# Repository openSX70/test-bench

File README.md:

# test-bench
universal SX70 PCB testes

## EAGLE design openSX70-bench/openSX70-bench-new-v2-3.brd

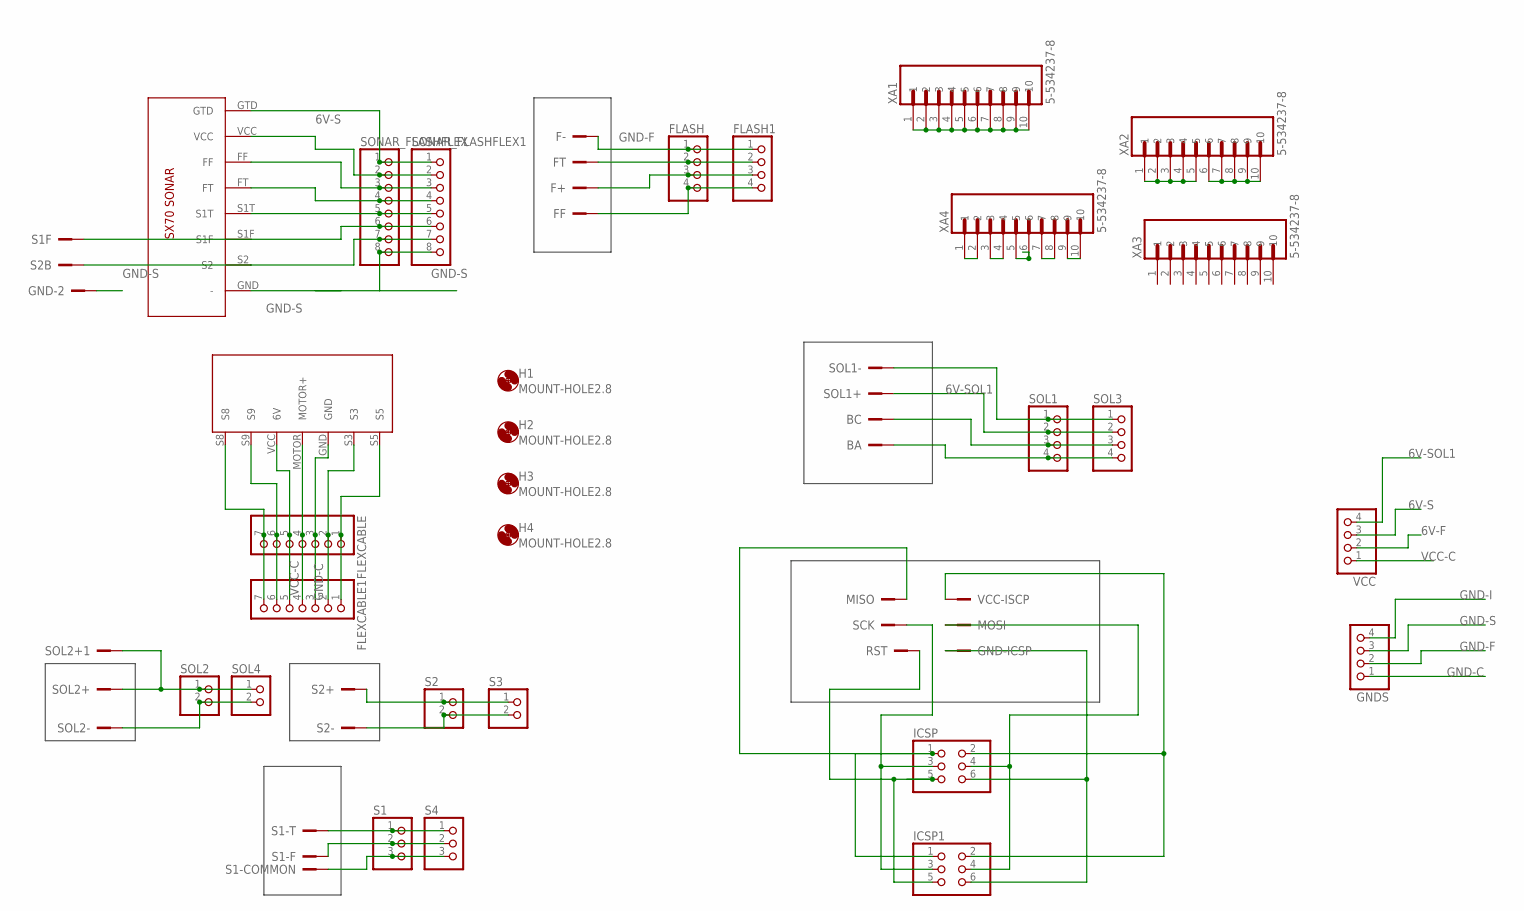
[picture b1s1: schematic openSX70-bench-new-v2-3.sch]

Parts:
BA: PINHEAD; 1X01
BC: PINHEAD; 1X01
F+: PINHEAD; 1X01
F-: PINHEAD; 1X01
FF: PINHEAD; 1X01
FLASH, FLASH1: PINHD-1X4; 1X04
FLEXCABLE, FLEXCABLE1: PINHD-1X7; 1X07
FT: PINHEAD; 1X01
GND-2: PINHEAD; 1X01
GND-ICSP: PINHEAD; 1X01
GNDS: PINHD-1X4; 1X04
H1, H2, H3, H4: MOUNT-HOLE2.8; 2,8
ICSP, ICSP1: PINHD-2X3; 2X03
MISO: PINHEAD; 1X01
MOSI: PINHEAD; 1X01
RST: PINHEAD; 1X01
S1, S4: PINHD-1X3; 1X03
S1-COMMON, S1-F, S1-T, S1F, S2+, S2-, S2B: PINHEAD; 1X01
S2, S3: PINHD-1X2; 1X02
SCK: PINHEAD; 1X01
SOL1, SOL3: PINHD-1X4; 1X04
SOL1+, SOL1-, SOL2+, SOL2+1, SOL2-: PINHEAD; 1X01
SOL2, SOL4: PINHD-1X2; 1X02
SONAR_FLASHFLEX, SONAR_FLASHFLEX1: PINHD-1X8; 1X08
U$1: SX70-7-PAD-HOLES-PROPER2
U$2: SX70-SONAR-FLASHFLEX-HOLES; SONAR-FLASHFLEX-HOLES
VCC: PINHD-1X4; 1X04
VCC-ISCP: PINHEAD; 1X01
XA1, XA2, XA3, XA4: 5-534237-8; TE_5-534237-8

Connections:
6V-F: F+.1, FLASH.3, FLASH1.3, VCC.2
6V-I: ICSP.2, ICSP1.2, VCC-ISCP.1
6V-S: SONAR_FLASHFLEX.2, SONAR_FLASHFLEX1.2, U$2.VCC, VCC.3
6V-SOL1: SOL1.2, SOL1+.1, SOL3.2, VCC.4
GND-C: FLEXCABLE.3, FLEXCABLE1.3, GNDS.1, U$1.GND
GND-F: F-.1, FLASH.1, FLASH1.1, GNDS.2
GND-I: GND-ICSP.1, GNDS.4, ICSP.6, ICSP1.6
GND-S: GND-2.1, GNDS.3, SONAR_FLASHFLEX.8, SONAR_FLASHFLEX1.8, U$2.GND (-)
unnamed: FLEXCABLE.7, FLEXCABLE1.7, U$1.S8
unnamed: FLEXCABLE.6, FLEXCABLE1.6, U$1.S9
unnamed: XA1.1, XA1.2, XA1.3, XA1.4, XA1.5, XA1.6, XA1.7, XA1.8, XA1.9, XA1.10
unnamed: FLEXCABLE.4, FLEXCABLE1.4, U$1.MOTOR (MOTOR+)
unnamed: XA4.1, XA4.2
unnamed: FLEXCABLE.2, FLEXCABLE1.2, U$1.S3
unnamed: FLEXCABLE.1, FLEXCABLE1.1, U$1.S5
unnamed: ICSP.1, ICSP1.1, MISO.1
unnamed: ICSP.3, ICSP1.3, SCK.1
unnamed: ICSP.5, ICSP1.5, RST.1
unnamed: XA4.3, XA4.4
unnamed: ICSP.4, ICSP1.4, MOSI.1
unnamed: S1F.1, SONAR_FLASHFLEX.6, SONAR_FLASHFLEX1.6, U$2.S1F
unnamed: SONAR_FLASHFLEX.5, SONAR_FLASHFLEX1.5, U$2.S1T
unnamed: SONAR_FLASHFLEX.1, SONAR_FLASHFLEX1.1, U$2.GTD
unnamed: SONAR_FLASHFLEX.3, SONAR_FLASHFLEX1.3, U$2.FF
unnamed: SONAR_FLASHFLEX.4, SONAR_FLASHFLEX1.4, U$2.FT
unnamed: XA4.5, XA4.6
unnamed: XA4.7, XA4.8
unnamed: S1.3, S1-COMMON.1, S4.3
unnamed: S1.2, S1-F.1, S4.2
unnamed: FLASH.2, FLASH1.2, FT.1
unnamed: S1.1, S1-T.1, S4.1
unnamed: FF.1, FLASH.4, FLASH1.4
unnamed: SOL1.1, SOL1-.1, SOL3.1
unnamed: XA4.9, XA4.10
unnamed: BC.1, SOL1.3, SOL3.3
unnamed: BA.1, SOL1.4, SOL3.4
unnamed: XA2.1, XA2.2, XA2.3, XA2.4, XA2.5
unnamed: XA2.6, XA2.7, XA2.8, XA2.9, XA2.10
unnamed: SOL2.1, SOL2+.1, SOL2+1.1, SOL4.1
unnamed: SOL2.2, SOL2-.1, SOL4.2
unnamed: S2.1, S2+.1, S3.1
unnamed: S2.2, S2-.1, S3.2
VCC-C: FLEXCABLE.5, FLEXCABLE1.5, U$1.VCC (6V), VCC.1

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
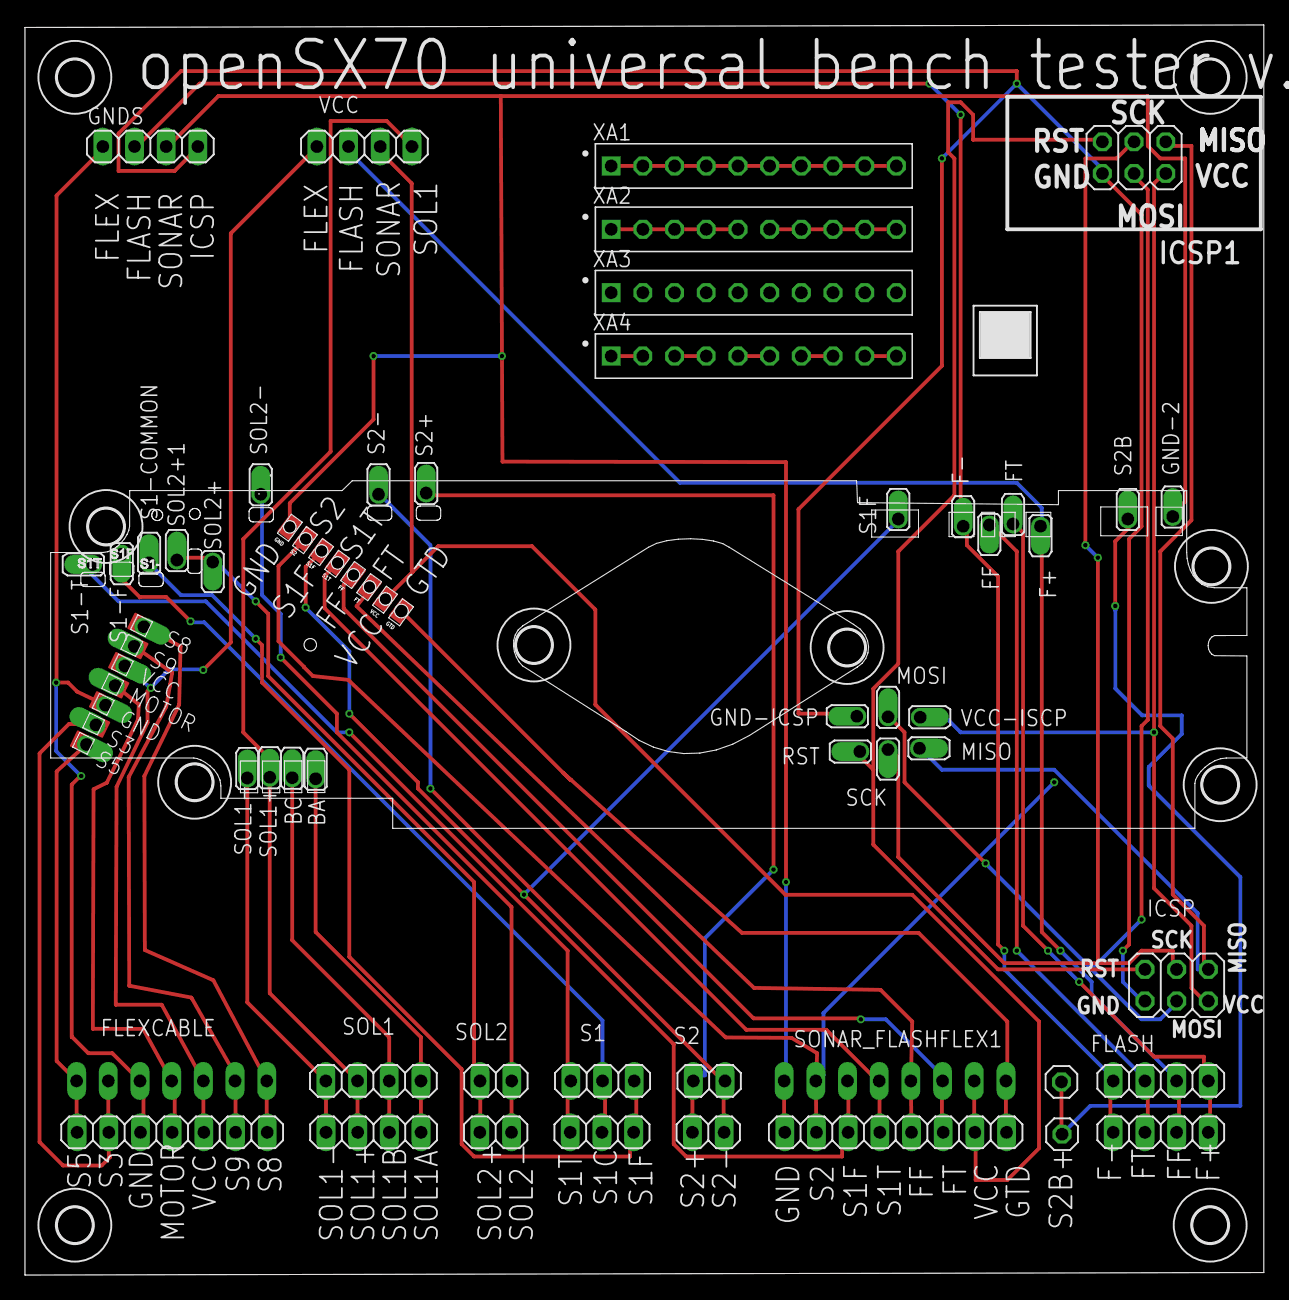
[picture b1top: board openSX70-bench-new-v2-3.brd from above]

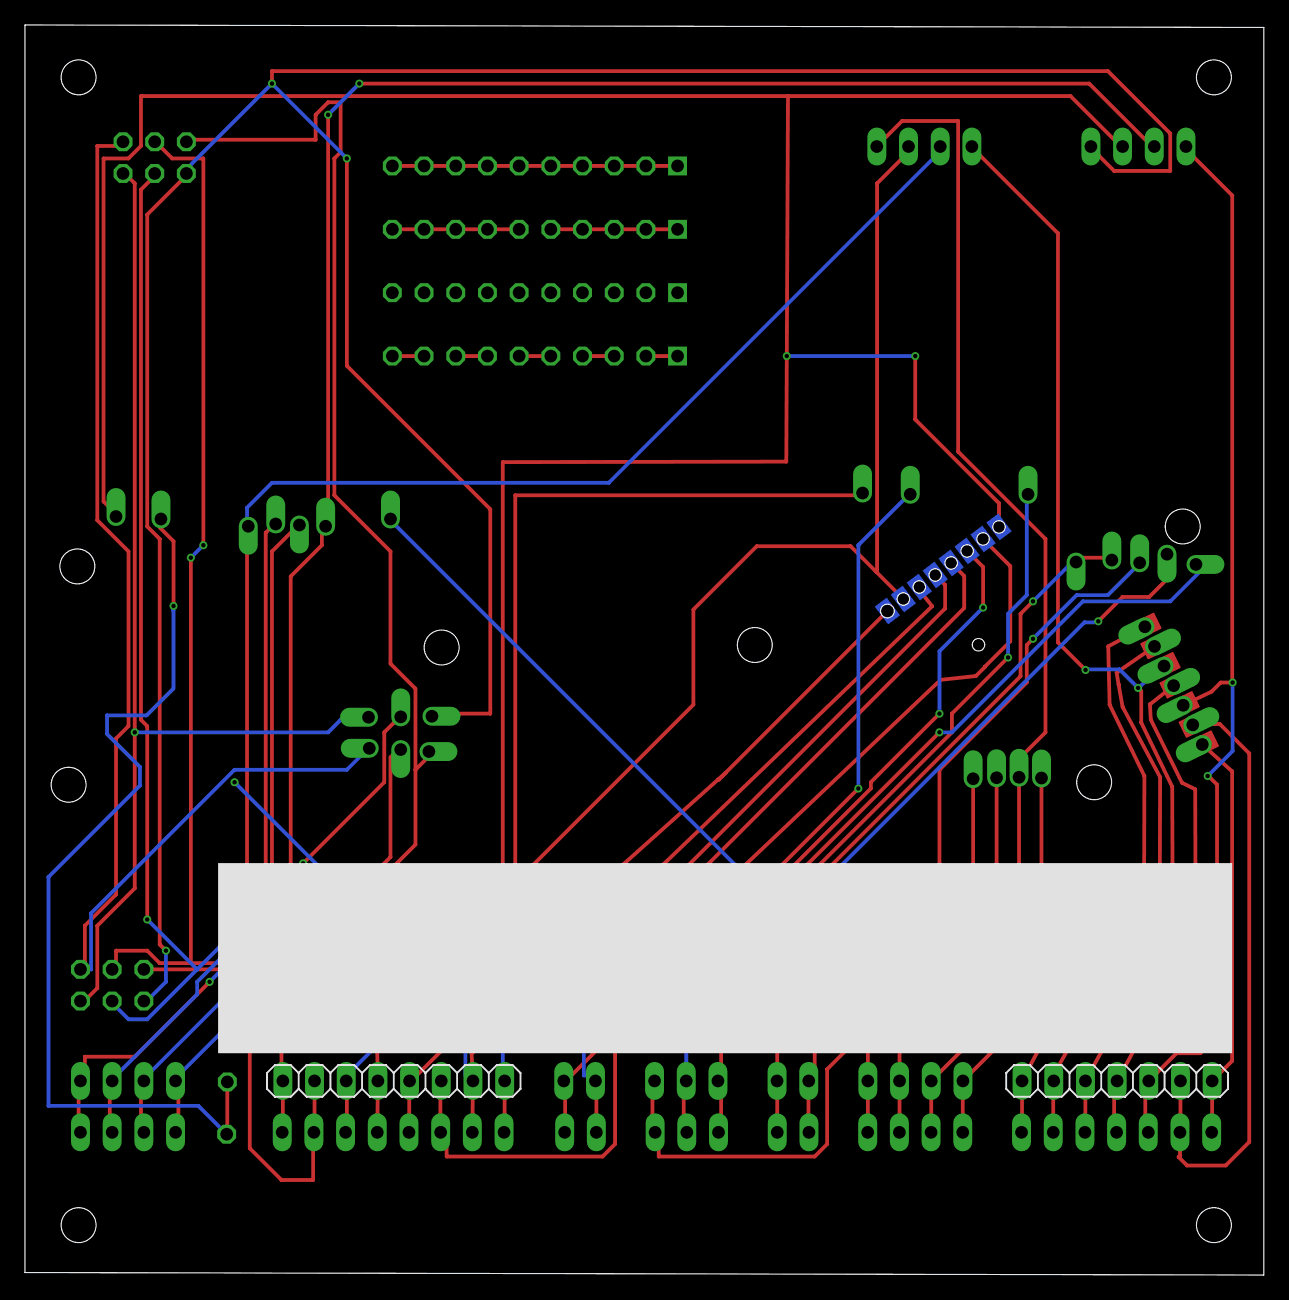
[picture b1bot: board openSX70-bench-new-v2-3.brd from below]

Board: 2 copper layers, 99.3 x 100.2 mm, 61 parts (2 on the bottom side), 45 nets.

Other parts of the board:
H5, H6, H7, H8, H9, H10: MOUNT-HOLE2.8; 2,8
JP1, JP2: 1X01

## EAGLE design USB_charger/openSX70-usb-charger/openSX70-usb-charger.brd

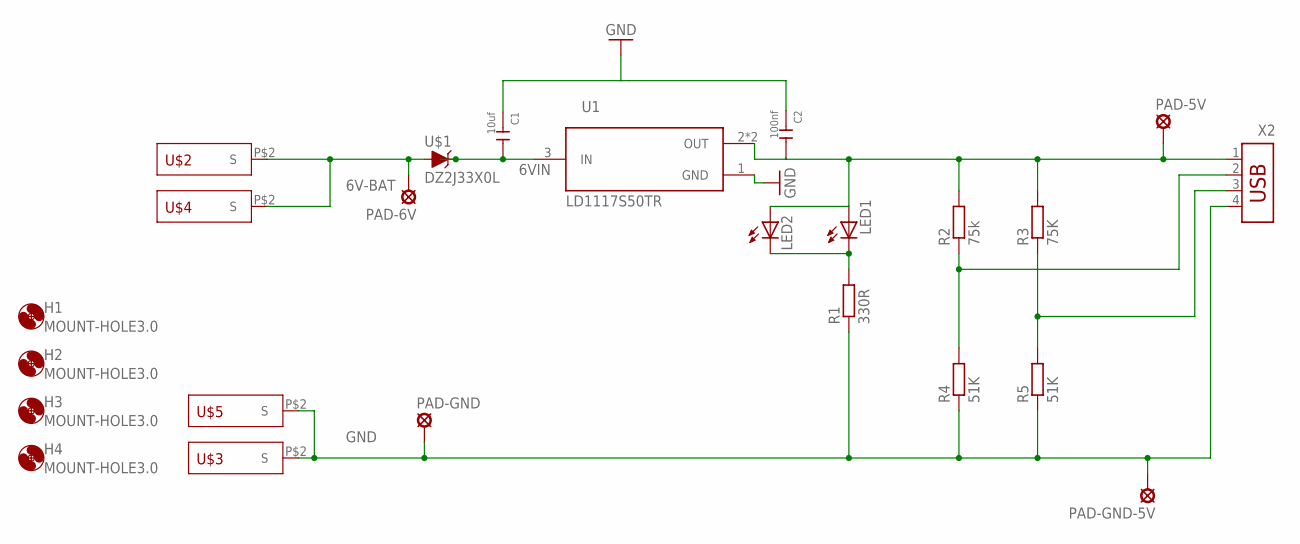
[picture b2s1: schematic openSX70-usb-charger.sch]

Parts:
C1: 10uf; C0603
C2: 100nf; C0603
H1, H2, H3, H4: MOUNT-HOLE3.0; 3,0
LED1: LED5MM
LED2: LEDCHIPLED_0805; CHIPLED_0805
PAD-5V, PAD-6V: LSP13
PAD-GND: LSP13
PAD-GND-5V: LSP13
R1: 330R; R0603
R2: 75k; R0603
R3: 75K; R0603
R4, R5: 51K; R0603
U1: LD1117S50TR; LD1117S50TR_SOT230P700X180-4N
U$1: DZ2J33X0L; SMINI2
U$2, U$3, U$4, U$5: BATTERY-PAD
X2: USB-787616; USB

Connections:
6V-BAT: PAD-6V.MP, U$1.P$2 (A), U$2.P$2, U$4.P$2
6VIN: C1.2, U1.3 (IN), U$1.P$1 (C)
GND: C1.1, C2.1, PAD-GND.MP, PAD-GND-5V.MP, R1.1, R4.1, R5.1, U1.1 (GND), U$3.P$2, U$5.P$2, X2.4
unnamed: LED1.K (C), LED2.C, R1.2
unnamed: C2.2, LED1.A, LED2.A, PAD-5V.MP, R2.2, R3.2, U1.2 (OUT), U1.4 (OUT), X2.1
unnamed: R2.1, R4.2, X2.2
unnamed: R3.1, R5.2, X2.3

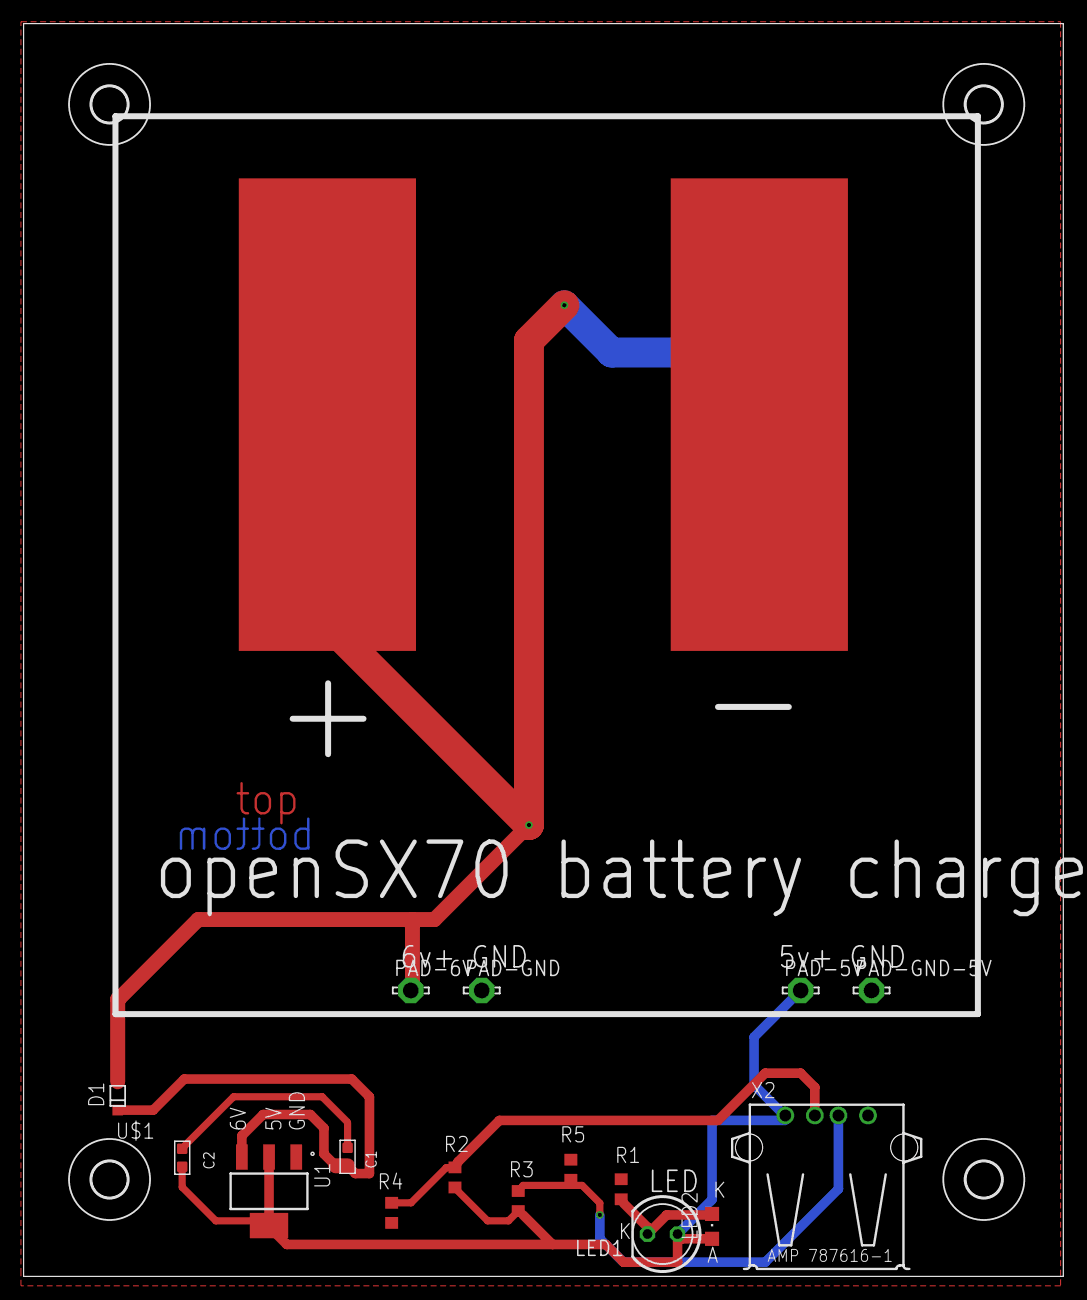
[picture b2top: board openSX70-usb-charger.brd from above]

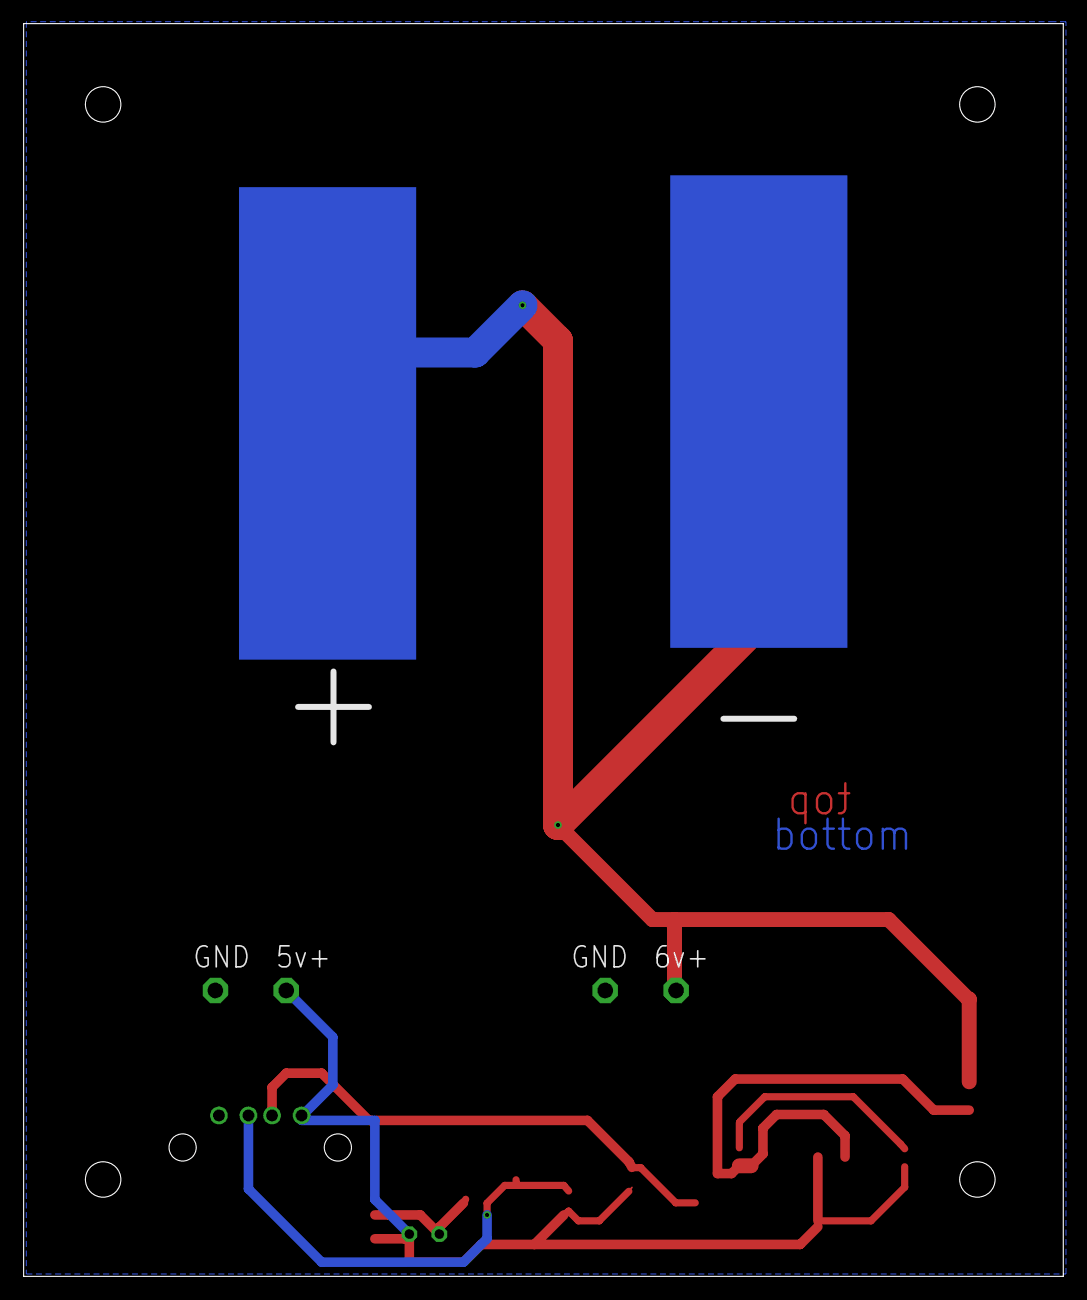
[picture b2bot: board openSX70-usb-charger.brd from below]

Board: 2 copper layers, 88.0 x 106.0 mm, 24 parts (2 on the bottom side), 7 nets.

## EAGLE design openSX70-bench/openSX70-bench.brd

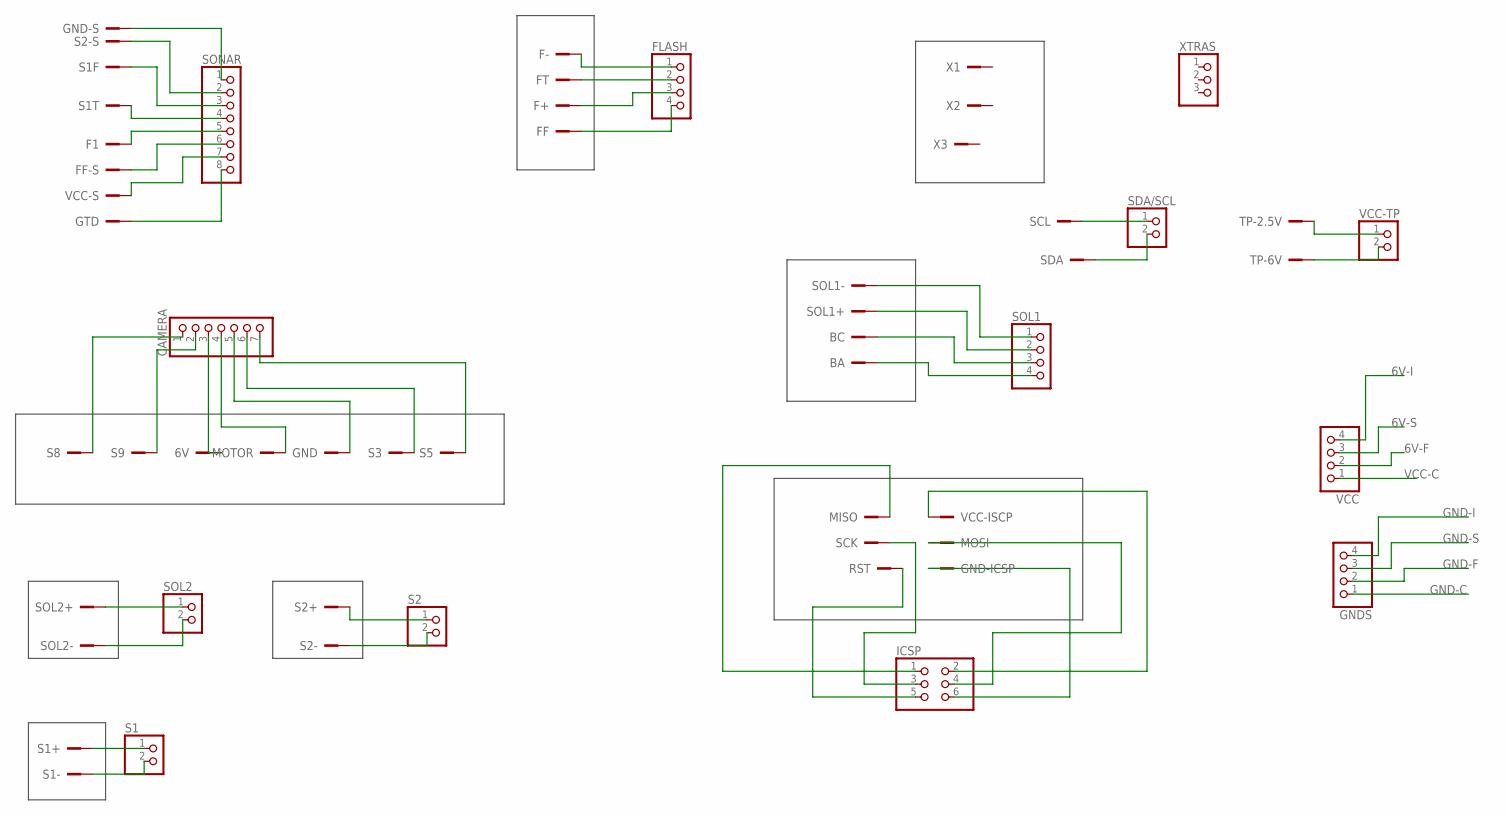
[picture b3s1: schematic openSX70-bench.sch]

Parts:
6V: PINHEAD; 1X01
BA: PINHEAD; 1X01
BC: PINHEAD; 1X01
CAMERA: PINHD-1X7; 1X07
F1: PINHEAD; 1X01
F+: PINHEAD; 1X01
F-: PINHEAD; 1X01
FF: PINHEAD; 1X01
FF-S: PINHEAD; 1X01
FLASH: PINHD-1X4; 1X04
FT: PINHEAD; 1X01
GND: PINHEAD; 1X01
GND-ICSP: PINHEAD; 1X01
GND-S: PINHEAD; 1X01
GNDS: PINHD-1X4; 1X04
GTD: PINHEAD; 1X01
ICSP: PINHD-2X3; 2X03
MISO: PINHEAD; 1X01
MOSI: PINHEAD; 1X01
MOTOR: PINHEAD; 1X01
RST: PINHEAD; 1X01
S1, S2: PINHD-1X2; 1X02
S1+, S1-, S1F, S1T, S2+, S2-, S2-S, S3, S5, S8, S9: PINHEAD; 1X01
SCK: PINHEAD; 1X01
SCL: PINHEAD; 1X01
SDA: PINHEAD; 1X01
SDA/SCL: PINHD-1X2; 1X02
SOL1: PINHD-1X4; 1X04
SOL1+, SOL1-, SOL2+, SOL2-: PINHEAD; 1X01
SOL2: PINHD-1X2; 1X02
SONAR: PINHD-1X8; 1X08
TP-2.5V, TP-6V: PINHEAD; 1X01
VCC: PINHD-1X4; 1X04
VCC-ISCP: PINHEAD; 1X01
VCC-S: PINHEAD; 1X01
VCC-TP: PINHD-1X2; 1X02
X1, X2, X3: PINHEAD; 1X01
XTRAS: PINHD-1X3; 1X03

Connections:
6V-F: F+.1, FLASH.3, VCC.2
6V-I: ICSP.2, VCC.4, VCC-ISCP.1
6V-S: SONAR.7, VCC.3, VCC-S.1
GND-C: CAMERA.5, GND.1, GNDS.1
GND-F: F-.1, FLASH.1, GNDS.2
GND-I: GND-ICSP.1, GNDS.4, ICSP.6
GND-S: GND-S.1, GNDS.3, SONAR.1
unnamed: CAMERA.1, S8.1
unnamed: CAMERA.2, S9.1
unnamed: CAMERA.4, MOTOR.1
unnamed: CAMERA.6, S3.1
unnamed: CAMERA.7, S5.1
unnamed: ICSP.1, MISO.1
unnamed: ICSP.3, SCK.1
unnamed: ICSP.5, RST.1
unnamed: ICSP.4, MOSI.1
unnamed: S2-S.1, SONAR.2
unnamed: S1F.1, SONAR.3
unnamed: S1T.1, SONAR.4
unnamed: F1.1, SONAR.5
unnamed: FF-S.1, SONAR.6
unnamed: GTD.1, SONAR.8
unnamed: FLASH.2, FT.1
unnamed: FF.1, FLASH.4
unnamed: SOL1.1, SOL1-.1
unnamed: SOL1.2, SOL1+.1
unnamed: BC.1, SOL1.3
unnamed: BA.1, SOL1.4
unnamed: SCL.1, SDA/SCL.1
unnamed: SDA.1, SDA/SCL.2
unnamed: TP-2.5V.1, VCC-TP.1
unnamed: TP-6V.1, VCC-TP.2
unnamed: SOL2.1, SOL2+.1
unnamed: SOL2.2, SOL2-.1
unnamed: S1.1, S1+.1
unnamed: S1.2, S1-.1
unnamed: S2.1, S2+.1
unnamed: S2.2, S2-.1
VCC-C: 6V.1, CAMERA.3, VCC.1

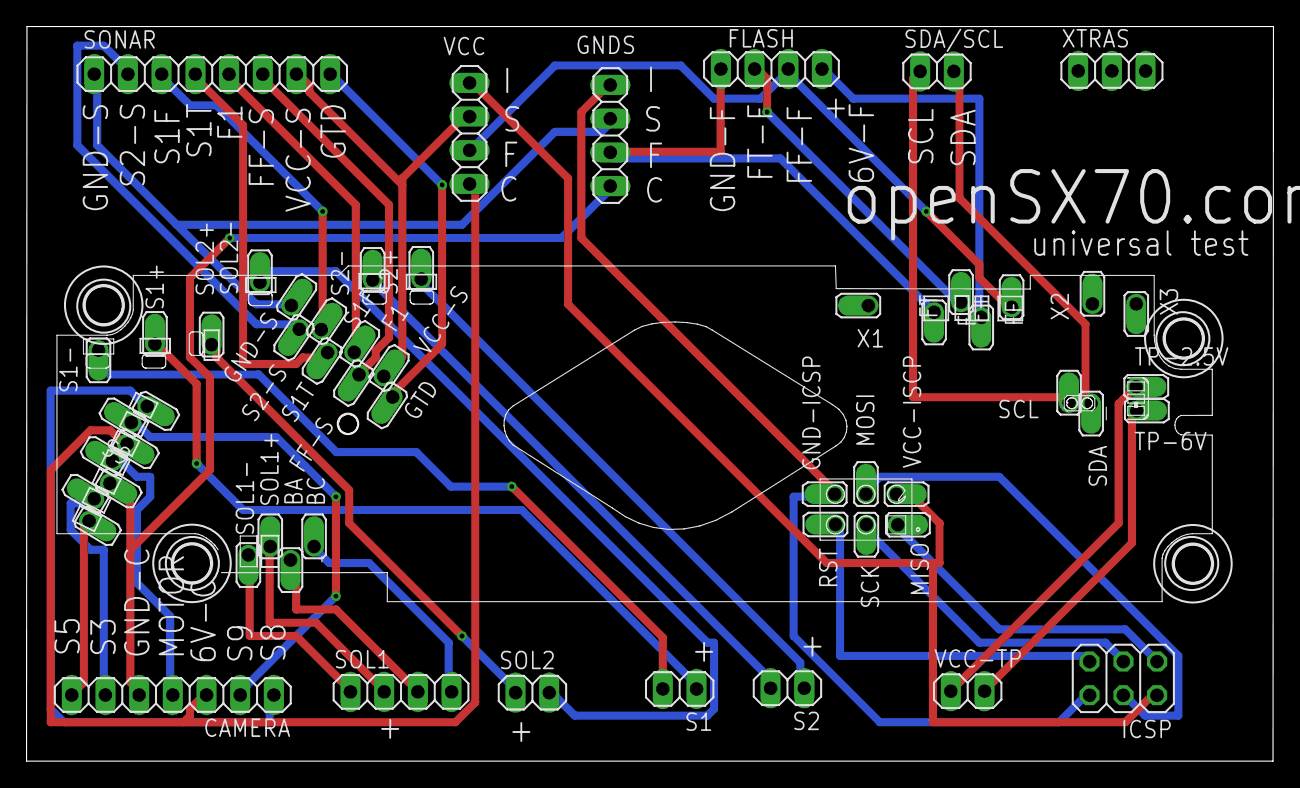
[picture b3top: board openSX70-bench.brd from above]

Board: 2 copper layers, 94.0 x 55.4 mm, 59 parts (0 on the bottom side), 39 nets.

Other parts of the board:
U$1, U$2, U$3, U$4: 2,8

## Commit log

2018-03-05 the openSX70 test bench files from the office
2018-10-15 new test bench
2018-10-20 Work in progress
2018-10-20 Working on the bench and on the charger
2018-10-22 working on the charger
2018-10-22 added photo-sized pcb outline to charger
2018-10-22 Working on the bench
2018-10-29 new USB charger design
2018-10-29 minor progress on the bench
2018-10-31 minor changes, waiting for PJK on new regulator
2018-11-06 the bench v.2
2018-11-06 new bench
2018-11-07 bench final-production
2019-01-04 no message
2019-01-11 New version
